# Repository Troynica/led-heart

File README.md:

# led-heart
Heart shaped LED board

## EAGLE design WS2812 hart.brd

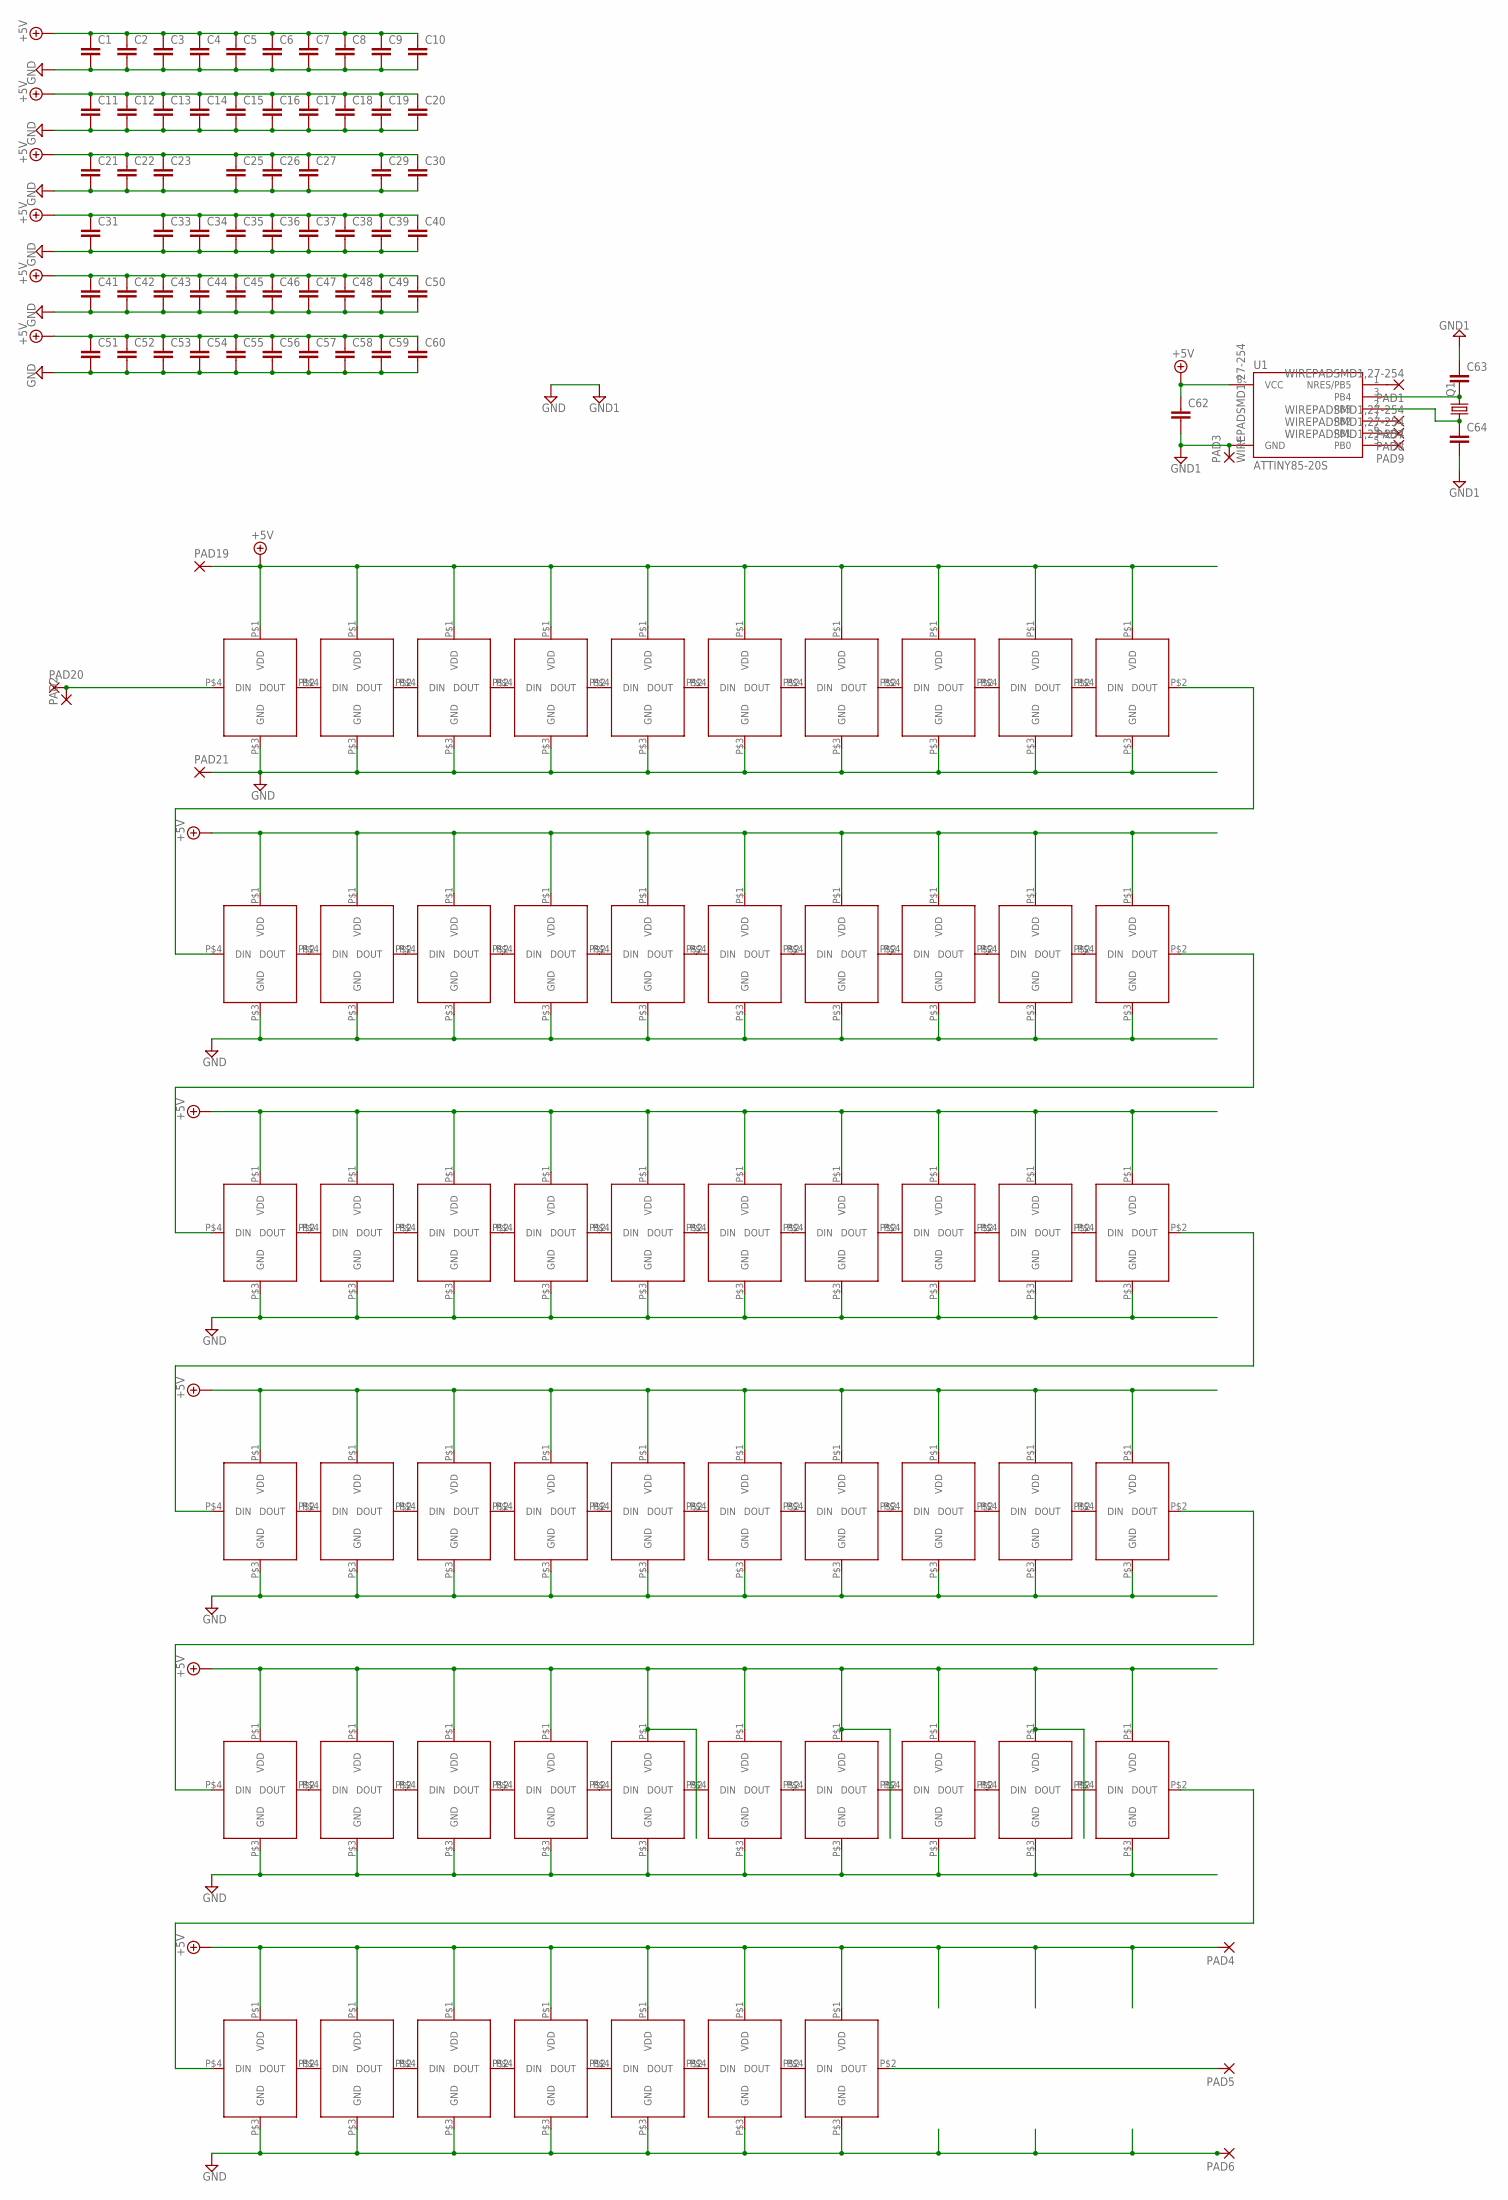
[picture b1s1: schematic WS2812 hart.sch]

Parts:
C1, C2, C3, C4, C5, C6, C7, C8, C9, C10, C11, C12, C13, C14, C15, C16, C18, C19, C20, C21, C22, C23, C25, C26, C27, C29, C30, C31, C33, C34, C35, C36, C37, C38, C39, C40, C41, C42, C43, C44, C45, C46, C47, C48, C49, C50, C51, C53, C54, C55, C56, C57, C58, C59, C60: C-EUC1206K; C1206K
C17, C52, C62: C-EUC0805K; C0805K
C63, C64: C-EUC0603K; C0603K
PAD1, PAD3, PAD7, PAD8, PAD9: WIREPADSMD1,27-254; SMD1,27-2,54
PAD2: SMD5; SMD2,54-5,08
PAD4, PAD5, PAD6, PAD19, PAD20, PAD21: 1,6/0,8
Q1: CRYSTALHC49S; HC49/S
U1: ATTINY85-20S; SOIC8_EIAJ_208MIL
U$1, U$2, U$3, U$4, U$5, U$6, U$7, U$8, U$9, U$10, U$11, U$12, U$13, U$14, U$15, U$16, U$17, U$18, U$19, U$20, U$21, U$22, U$23, U$24, U$25, U$26, U$27, U$28, U$29, U$30, U$31, U$32, U$33, U$34, U$35, U$36, U$37, U$38, U$39, U$40, U$41, U$42, U$43, U$44, U$45, U$46, U$47, U$48, U$49, U$50, U$51, U$52, U$53, U$54, U$55, U$56, U$57: WS2812B; PLCC-4

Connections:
+5V: C1.1, C2.1, C3.1, C4.1, C5.1, C6.1, C7.1, C8.1, C9.1, C10.1, C11.1, C12.1, C13.1, C14.1, C15.1, C16.1, C17.1, C18.1, C19.1, C20.1, C21.1, C22.1, C23.1, C25.1, C26.1, C27.1, C29.1, C30.1, C31.1, C33.1, C34.1, C35.1, C36.1, C37.1, C38.1, C39.1, C40.1, C41.1, C42.1, C43.1, C44.1, C45.1, C46.1, C47.1, C48.1, C49.1, C50.1, C51.1, C52.1, C53.1, C54.1, C55.1, C56.1, C57.1, C58.1, C59.1, C60.1, C62.1, PAD4.1, PAD19.1, U1.8 (VCC), U$1.P$1 (VDD), U$2.P$1 (VDD), U$3.P$1 (VDD), U$4.P$1 (VDD), U$5.P$1 (VDD), U$6.P$1 (VDD), U$7.P$1 (VDD), U$8.P$1 (VDD), U$9.P$1 (VDD), U$10.P$1 (VDD), U$11.P$1 (VDD), U$12.P$1 (VDD), U$13.P$1 (VDD), U$14.P$1 (VDD), U$15.P$1 (VDD), U$16.P$1 (VDD), U$17.P$1 (VDD), U$18.P$1 (VDD), U$19.P$1 (VDD), U$20.P$1 (VDD), U$21.P$1 (VDD), U$22.P$1 (VDD), U$23.P$1 (VDD), U$24.P$1 (VDD), U$25.P$1 (VDD), U$26.P$1 (VDD), U$27.P$1 (VDD), U$28.P$1 (VDD), U$29.P$1 (VDD), U$30.P$1 (VDD), U$31.P$1 (VDD), U$32.P$1 (VDD), U$33.P$1 (VDD), U$34.P$1 (VDD), U$35.P$1 (VDD), U$36.P$1 (VDD), U$37.P$1 (VDD), U$38.P$1 (VDD), U$39.P$1 (VDD), U$40.P$1 (VDD), U$41.P$1 (VDD), U$42.P$1 (VDD), U$43.P$1 (VDD), U$44.P$1 (VDD), U$45.P$1 (VDD), U$46.P$1 (VDD), U$47.P$1 (VDD), U$48.P$1 (VDD), U$49.P$1 (VDD), U$50.P$1 (VDD), U$51.P$1 (VDD), U$52.P$1 (VDD), U$53.P$1 (VDD), U$54.P$1 (VDD), U$55.P$1 (VDD), U$56.P$1 (VDD), U$57.P$1 (VDD)
GND: C1.2, C2.2, C3.2, C4.2, C5.2, C6.2, C7.2, C8.2, C9.2, C10.2, C11.2, C12.2, C13.2, C14.2, C15.2, C16.2, C17.2, C18.2, C19.2, C20.2, C21.2, C22.2, C23.2, C25.2, C26.2, C27.2, C29.2, C30.2, C31.2, C33.2, C34.2, C35.2, C36.2, C37.2, C38.2, C39.2, C40.2, C41.2, C42.2, C43.2, C44.2, C45.2, C46.2, C47.2, C48.2, C49.2, C50.2, C51.2, C52.2, C53.2, C54.2, C55.2, C56.2, C57.2, C58.2, C59.2, C60.2, C62.2, C63.1, C64.2, PAD3.1, PAD6.1, PAD21.1, U1.4 (GND), U$1.P$3 (GND), U$2.P$3 (GND), U$3.P$3 (GND), U$4.P$3 (GND), U$5.P$3 (GND), U$6.P$3 (GND), U$7.P$3 (GND), U$8.P$3 (GND), U$9.P$3 (GND), U$10.P$3 (GND), U$11.P$3 (GND), U$12.P$3 (GND), U$13.P$3 (GND), U$14.P$3 (GND), U$15.P$3 (GND), U$16.P$3 (GND), U$17.P$3 (GND), U$18.P$3 (GND), U$19.P$3 (GND), U$20.P$3 (GND), U$21.P$3 (GND), U$22.P$3 (GND), U$23.P$3 (GND), U$24.P$3 (GND), U$25.P$3 (GND), U$26.P$3 (GND), U$27.P$3 (GND), U$28.P$3 (GND), U$29.P$3 (GND), U$30.P$3 (GND), U$31.P$3 (GND), U$32.P$3 (GND), U$33.P$3 (GND), U$34.P$3 (GND), U$35.P$3 (GND), U$36.P$3 (GND), U$37.P$3 (GND), U$38.P$3 (GND), U$39.P$3 (GND), U$40.P$3 (GND), U$41.P$3 (GND), U$42.P$3 (GND), U$43.P$3 (GND), U$44.P$3 (GND), U$45.P$3 (GND), U$46.P$3 (GND), U$47.P$3 (GND), U$48.P$3 (GND), U$49.P$3 (GND), U$50.P$3 (GND), U$51.P$3 (GND), U$52.P$3 (GND), U$53.P$3 (GND), U$54.P$3 (GND), U$55.P$3 (GND), U$56.P$3 (GND), U$57.P$3 (GND)
unnamed: U$41.P$2 (DOUT), U$42.P$4 (DIN)
unnamed: U$2.P$2 (DOUT), U$3.P$4 (DIN)
unnamed: U$3.P$2 (DOUT), U$4.P$4 (DIN)
unnamed: U$4.P$2 (DOUT), U$5.P$4 (DIN)
unnamed: U$5.P$2 (DOUT), U$6.P$4 (DIN)
unnamed: U$6.P$2 (DOUT), U$7.P$4 (DIN)
unnamed: U$7.P$2 (DOUT), U$8.P$4 (DIN)
unnamed: U$8.P$2 (DOUT), U$9.P$4 (DIN)
unnamed: U$9.P$2 (DOUT), U$10.P$4 (DIN)
unnamed: U$11.P$2 (DOUT), U$12.P$4 (DIN)
unnamed: U$1.P$4 (DIN), U$10.P$2 (DOUT)
unnamed: U$1.P$2 (DOUT), U$41.P$4 (DIN)
unnamed: U$12.P$2 (DOUT), U$13.P$4 (DIN)
unnamed: U$13.P$2 (DOUT), U$14.P$4 (DIN)
unnamed: U$14.P$2 (DOUT), U$15.P$4 (DIN)
unnamed: U$15.P$2 (DOUT), U$16.P$4 (DIN)
unnamed: U$16.P$2 (DOUT), U$17.P$4 (DIN)
unnamed: U$17.P$2 (DOUT), U$18.P$4 (DIN)
unnamed: U$18.P$2 (DOUT), U$19.P$4 (DIN)
unnamed: U$42.P$2 (DOUT), U$43.P$4 (DIN)
unnamed: U$19.P$2 (DOUT), U$20.P$4 (DIN)
unnamed: U$2.P$4 (DIN), U$20.P$2 (DOUT)
unnamed: U$21.P$2 (DOUT), U$22.P$4 (DIN)
unnamed: U$22.P$2 (DOUT), U$23.P$4 (DIN)
unnamed: U$23.P$2 (DOUT), U$24.P$4 (DIN)
unnamed: U$24.P$2 (DOUT), U$25.P$4 (DIN)
unnamed: U$25.P$2 (DOUT), U$26.P$4 (DIN)
unnamed: U$26.P$2 (DOUT), U$27.P$4 (DIN)
unnamed: U$27.P$2 (DOUT), U$28.P$4 (DIN)
unnamed: U$28.P$2 (DOUT), U$29.P$4 (DIN)
unnamed: U$21.P$4 (DIN), U$40.P$2 (DOUT)
unnamed: U$29.P$2 (DOUT), U$30.P$4 (DIN)
unnamed: U$11.P$4 (DIN), U$30.P$2 (DOUT)
unnamed: U$31.P$2 (DOUT), U$32.P$4 (DIN)
unnamed: U$32.P$2 (DOUT), U$33.P$4 (DIN)
unnamed: U$33.P$2 (DOUT), U$34.P$4 (DIN)
unnamed: U$34.P$2 (DOUT), U$35.P$4 (DIN)
unnamed: U$35.P$2 (DOUT), U$36.P$4 (DIN)
unnamed: U$36.P$2 (DOUT), U$37.P$4 (DIN)
unnamed: U$37.P$2 (DOUT), U$38.P$4 (DIN)
unnamed: U$38.P$2 (DOUT), U$39.P$4 (DIN)
unnamed: PAD2.1, PAD20.1, U$31.P$4 (DIN)
unnamed: U$39.P$2 (DOUT), U$40.P$4 (DIN)
unnamed: U$43.P$2 (DOUT), U$44.P$4 (DIN)
unnamed: U$44.P$2 (DOUT), U$45.P$4 (DIN)
unnamed: U$45.P$2 (DOUT), U$46.P$4 (DIN)
unnamed: U$46.P$2 (DOUT), U$47.P$4 (DIN)
unnamed: U$47.P$2 (DOUT), U$48.P$4 (DIN)
unnamed: U$48.P$2 (DOUT), U$49.P$4 (DIN)
unnamed: U$49.P$2 (DOUT), U$50.P$4 (DIN)
unnamed: U$50.P$2 (DOUT), U$51.P$4 (DIN)
unnamed: C63.2, Q1.2, U1.3 (PB4)
unnamed: U$51.P$2 (DOUT), U$52.P$4 (DIN)
unnamed: U$52.P$2 (DOUT), U$53.P$4 (DIN)
unnamed: U$53.P$2 (DOUT), U$54.P$4 (DIN)
unnamed: U$54.P$2 (DOUT), U$55.P$4 (DIN)
unnamed: U$55.P$2 (DOUT), U$56.P$4 (DIN)
unnamed: U$56.P$2 (DOUT), U$57.P$4 (DIN)
unnamed: C64.1, Q1.1, U1.2 (PB3)
unnamed: PAD1.1, U1.1 (NRES/PB5)
unnamed: PAD5.1, U$57.P$2 (DOUT)
unnamed: PAD7.1, U1.7 (PB2)
unnamed: PAD8.1, U1.6 (PB1)
unnamed: PAD9.1, U1.5 (PB0)

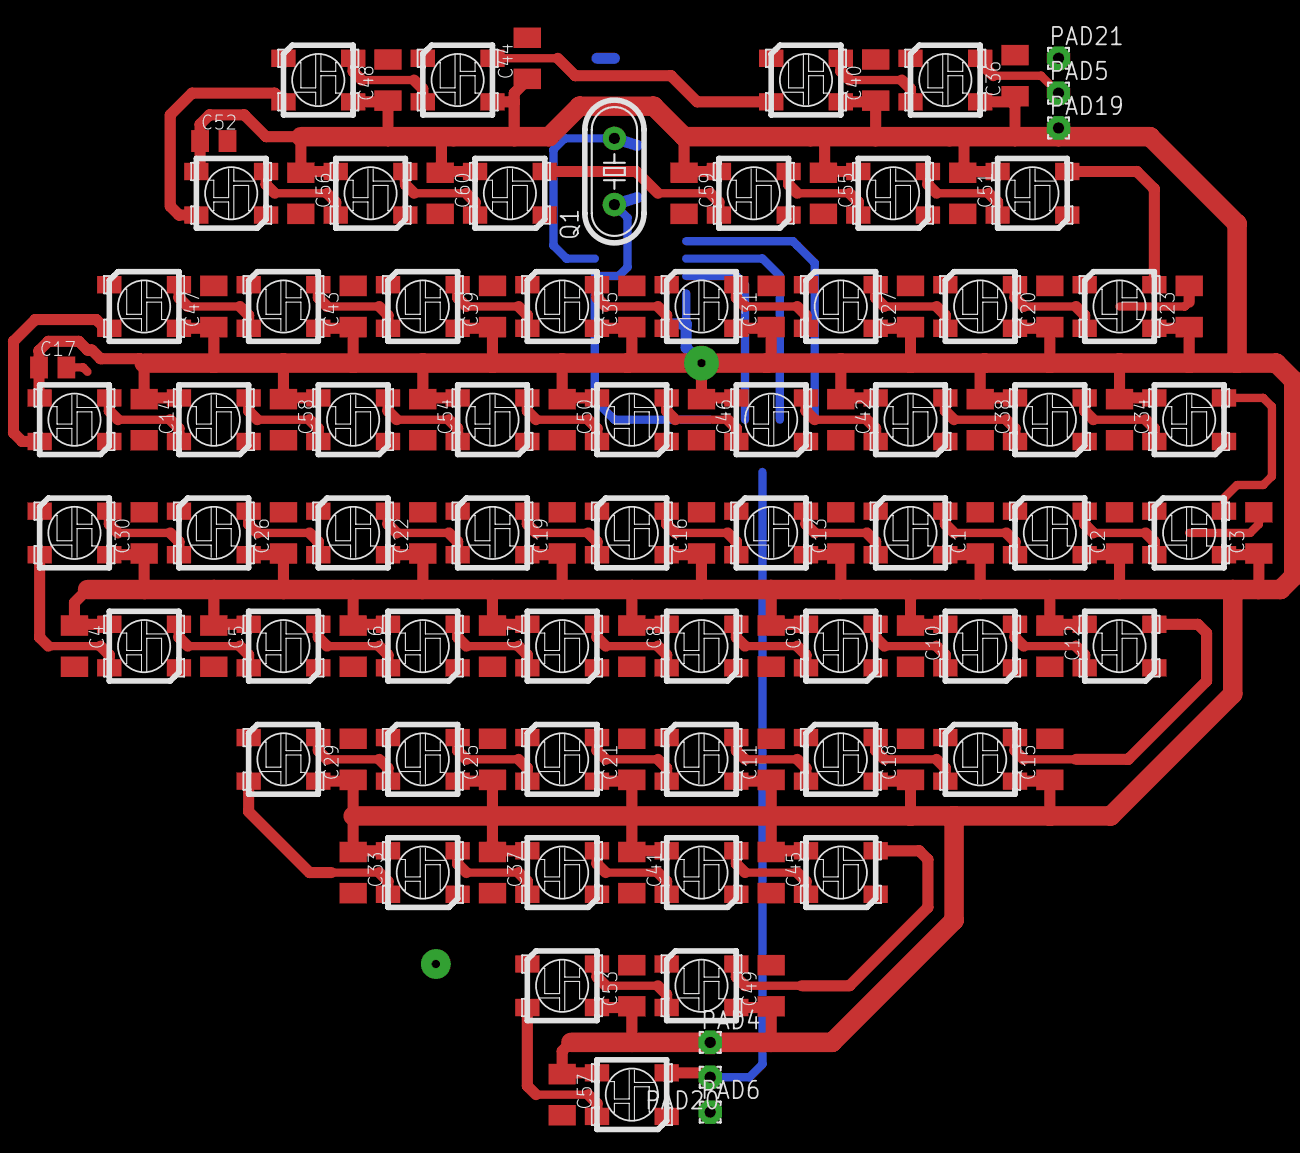
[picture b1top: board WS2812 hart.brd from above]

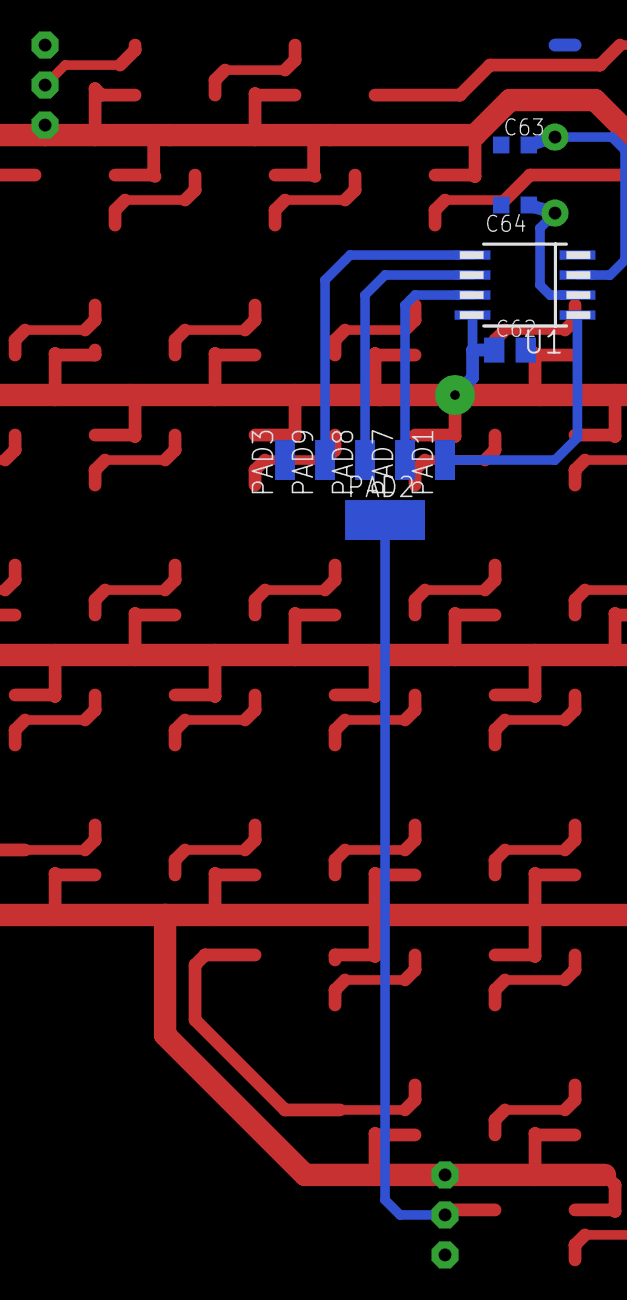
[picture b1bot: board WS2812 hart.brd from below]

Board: 2 copper layers, 131 parts (10 on the bottom side), 66 nets.

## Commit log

2015-12-04 Replaced symlinks with their original files
